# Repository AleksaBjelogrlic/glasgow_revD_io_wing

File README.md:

# glasgow_revD_io_wing

Modular test board for Glasgow RevD IO ports. Four of these will connect to a core board to form a complete revD prototype. Doing unconstrained and modular designs will speed up iteration and get us to a finalized design faster.

## Design Goals:

### 1.2V VIO support

- Use 74AXP1T45 level shifters as per [Glasgow #283](https://github.com/GlasgowEmbedded/glasgow/issues/283). 
- No GPIO expander will support this voltage so we have to do something clever for the programmable pulls.
- Pulldowns added on DIR pins as per [Glasgow #552, option 2](https://github.com/GlasgowEmbedded/glasgow/issues/552).
- Option 3 will not work at VIO = 5V as DIR is on the port A side and would be fed with a 3.3V signal, which is lower than the 3.5V threshold for VCCA = 5V.

### Increase VIO output current and support true 5V VIO

- Use a buck-boost regulator, TPS631012 eliminates the need for a DAC as well
- Max 1.5A on each port, can go up to 5.5V regardless of VUSB

### Make the most out of any USB host without browning out

- Adustable current limits on all VIO regulator inputs for 500mA, 1.5A, and 3A capable USB hosts  

### Add a user analog input

- Use the two free pins on each Glasgow port
- Single ended or diff, for voltage and current monitoring on the user's board

### Test new ESD diode array

- [Glasgow #765](https://github.com/GlasgowEmbedded/glasgow/issues/765)

### Improve schematic readablity

- Make the functions of the IO ports as clear as possible from first glance

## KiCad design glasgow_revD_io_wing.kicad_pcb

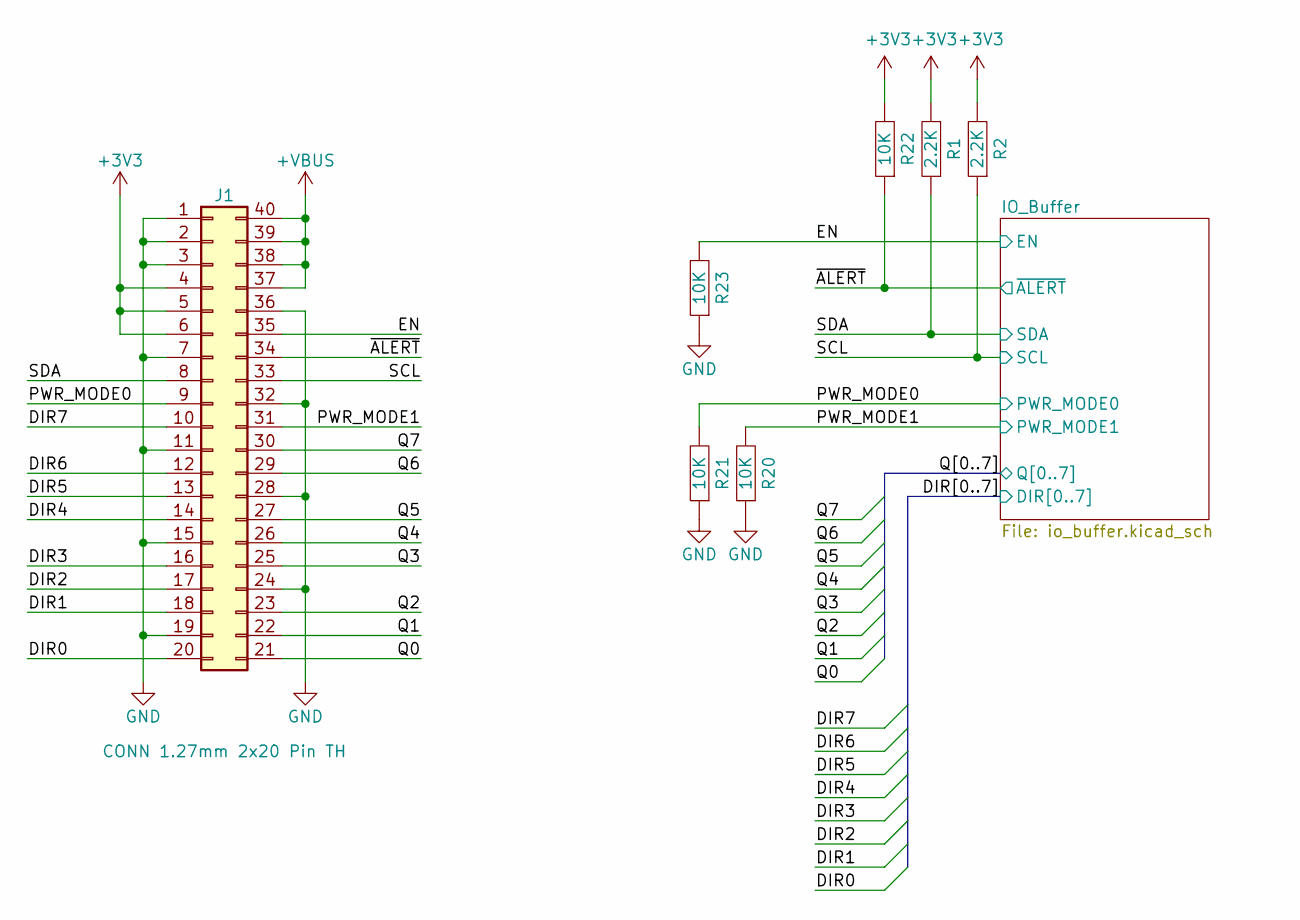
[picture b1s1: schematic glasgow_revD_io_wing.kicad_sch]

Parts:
J1: CONN 1.27mm 2x20 Pin TH; PinHeader_2x20_P1.27mm_Vertical
R1, R2: 2.2K; GEN_R_0402; TOLERANCE 1%; MANUFACTURER PART NUMBER RC0402FR-132K2L
R20, R21, R22, R23: 10K; GEN_R_0402; TOLERANCE 1%; MANUFACTURER PART NUMBER ERJ-2RKF1002X

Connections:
+3V3: J1.4, J1.5, J1.6, R1.1, R2.1, R22.2; also elsewhere on the board
+VBUS: J1.37, J1.38, J1.39, J1.40; also elsewhere on the board
/DIR0: J1.20; also elsewhere on the board
/DIR1: J1.18; also elsewhere on the board
/DIR2: J1.17; also elsewhere on the board
/DIR3: J1.16; also elsewhere on the board
/DIR4: J1.14; also elsewhere on the board
/DIR5: J1.13; also elsewhere on the board
/DIR6: J1.12; also elsewhere on the board
/DIR7: J1.10; also elsewhere on the board
/EN: J1.35, R23.2; also elsewhere on the board
/PWR_MODE0: J1.9, R21.2; also elsewhere on the board
/PWR_MODE1: J1.31, R20.2; also elsewhere on the board
/Q0: J1.21; also elsewhere on the board
/Q1: J1.22; also elsewhere on the board
/Q2: J1.23; also elsewhere on the board
/Q3: J1.25; also elsewhere on the board
/Q4: J1.26; also elsewhere on the board
/Q5: J1.27; also elsewhere on the board
/Q6: J1.29; also elsewhere on the board
/Q7: J1.30; also elsewhere on the board
/SCL: J1.33, R2.2; also elsewhere on the board
/SDA: J1.8, R1.2; also elsewhere on the board
/~ALERT: J1.34, R22.1; also elsewhere on the board
GND: J1.1, J1.2, J1.3, J1.7, J1.11, J1.15, J1.19, J1.24, J1.28, J1.32, J1.36, R20.1, R21.1, R23.1; also elsewhere on the board

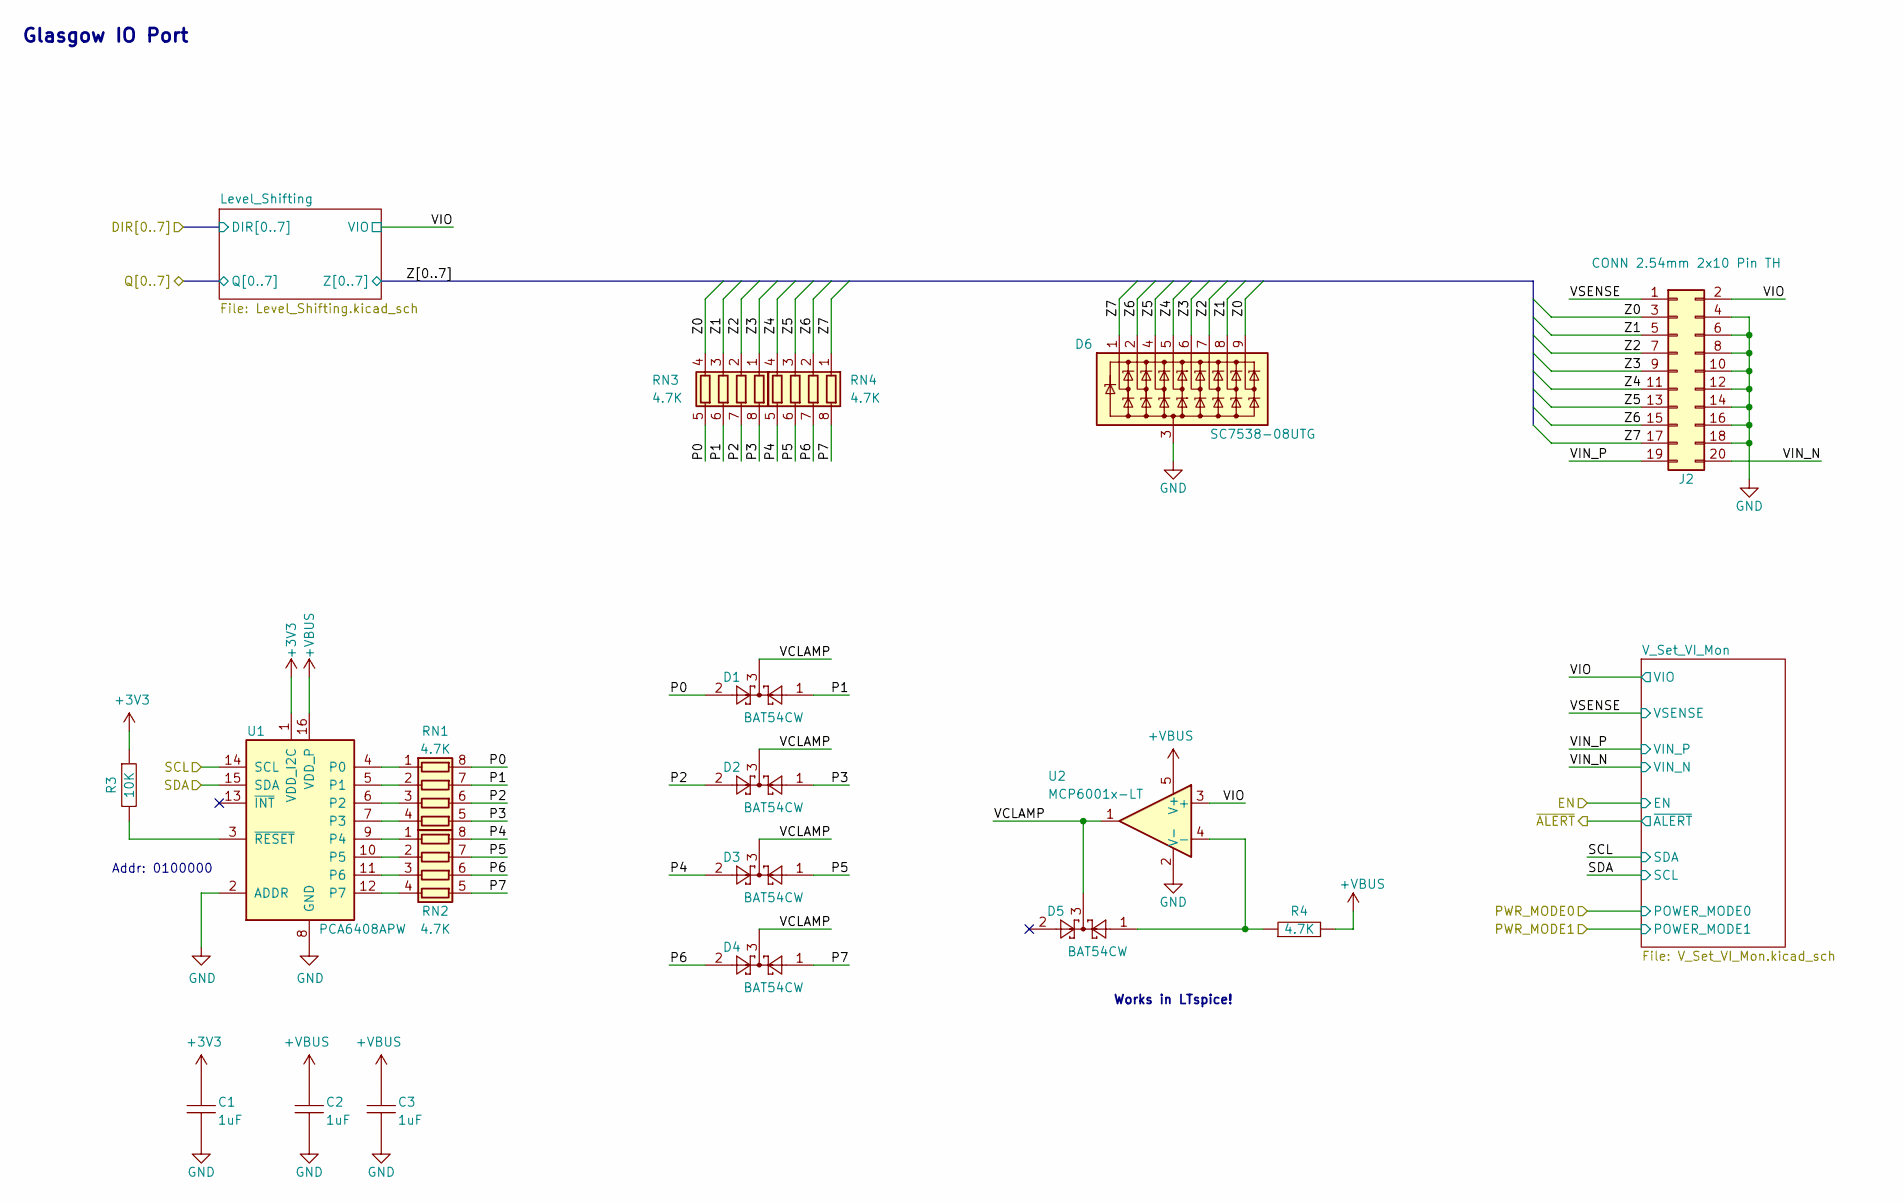
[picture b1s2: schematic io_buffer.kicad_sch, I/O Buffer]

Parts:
C1, C2, C3: 1uF; GEN_C_0402; VOLTAGE RATING 25V; MANUFACTURER PART NUMBER GRM155R61E105KA12D
D1, D2, D3, D4, D5: BAT54CW; SOT-323_SC-70; MANUFACTURER PART NUMBER BAT54CW-7-F
D6: SC7538-08UTG; Littelfuse_UDFN-9_1.0x3.8mm_P0.5mm; MANUFACTURER PART NUMBER SC7538-08UTG
J2: CONN 2.54mm 2x10 Pin TH; IDC-Header_2x10_P2.54mm_Vertical; MANUFACTURER PART NUMBER 87834-2019
R3: 10K; GEN_R_0402; TOLERANCE 1%; MANUFACTURER PART NUMBER ERJ-2RKF1002X
R4: 4.7K; GEN_R_0402; TOLERANCE 1%; MANUFACTURER PART NUMBER ERJ-2RKF4701X
RN1, RN2, RN3, RN4: 4.7K; R_Array_Convex_4x0402; MANUFACTURER PART NUMBER YC124-FR-074K7L
U1: PCA6408APW; TSSOP-16_4.4x5mm_P0.65mm; MANUFACTURER PART NUMBER PCA6408APW
U2: MCP6001x-LT; SOT-353_SC-70-5; MANUFACTURER PART NUMBER MCP6001T-I/LT

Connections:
+3V3: C1.1, R3.1, U1.1 (VDD_I2C); also elsewhere on the board
+VBUS: C2.1, C3.1, R4.1, U1.16 (VDD_P), U2.5 (V+); also elsewhere on the board
/IO_Buffer/P0: D1.2, RN1.8 (R1.2), RN3.5 (R4.2)
/IO_Buffer/P1: D1.1, RN1.7 (R2.2), RN3.6 (R3.2)
/IO_Buffer/P2: D2.2, RN1.6 (R3.2), RN3.7 (R2.2)
/IO_Buffer/P3: D2.1, RN1.5 (R4.2), RN3.8 (R1.2)
/IO_Buffer/P4: D3.2, RN2.8 (R1.2), RN4.5 (R4.2)
/IO_Buffer/P5: D3.1, RN2.7 (R2.2), RN4.6 (R3.2)
/IO_Buffer/P6: D4.2, RN2.6 (R3.2), RN4.7 (R2.2)
/IO_Buffer/P7: D4.1, RN2.5 (R4.2), RN4.8 (R1.2)
/IO_Buffer/VCLAMP: D1.3, D2.3, D3.3, D4.3, D5.3, U2.1
/IO_Buffer/VIN_N: J2.20; also elsewhere on the board
/IO_Buffer/VIN_P: J2.19; also elsewhere on the board
/IO_Buffer/VIO: J2.2, U2.3 (+); also elsewhere on the board
/IO_Buffer/VSENSE: J2.1; also elsewhere on the board
/IO_Buffer/Z0: D6.9 (K8), J2.3, RN3.4 (R4.1); also elsewhere on the board
/IO_Buffer/Z1: D6.8 (K7), J2.5, RN3.3 (R3.1); also elsewhere on the board
/IO_Buffer/Z2: D6.7 (K6), J2.7, RN3.2 (R2.1); also elsewhere on the board
/IO_Buffer/Z3: D6.6 (K5), J2.9, RN3.1 (R1.1); also elsewhere on the board
/IO_Buffer/Z4: D6.5 (K4), J2.11, RN4.4 (R4.1); also elsewhere on the board
/IO_Buffer/Z5: D6.4 (K3), J2.13, RN4.3 (R3.1); also elsewhere on the board
/IO_Buffer/Z6: D6.2 (K2), J2.15, RN4.2 (R2.1); also elsewhere on the board
/IO_Buffer/Z7: D6.1 (K1), J2.17, RN4.1 (R1.1); also elsewhere on the board
/SCL: U1.14 (SCL); also elsewhere on the board
/SDA: U1.15 (SDA); also elsewhere on the board
GND: C1.2, C2.2, C3.2, D6.3 (A), J2.4, J2.6, J2.8, J2.10, J2.12, J2.14, J2.16, J2.18, U1.2 (ADDR), U1.8 (GND), U2.2 (V-); also elsewhere on the board
unnamed: RN1.1 (R1.1), U1.4 (P0)
unnamed: RN1.2 (R2.1), U1.5 (P1)
unnamed: RN1.3 (R3.1), U1.6 (P2)
unnamed: RN1.4 (R4.1), U1.7 (P3)
unnamed: RN2.1 (R1.1), U1.9 (P4)
unnamed: RN2.2 (R2.1), U1.10 (P5)
unnamed: RN2.3 (R3.1), U1.11 (P6)
unnamed: RN2.4 (R4.1), U1.12 (P7)
unnamed: R3.2, U1.3 (~RESET)
unnamed: D5.1, R4.2, U2.4 (-)

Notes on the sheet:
Glasgow IO Port
Addr: 0100000
Works in LTspice!

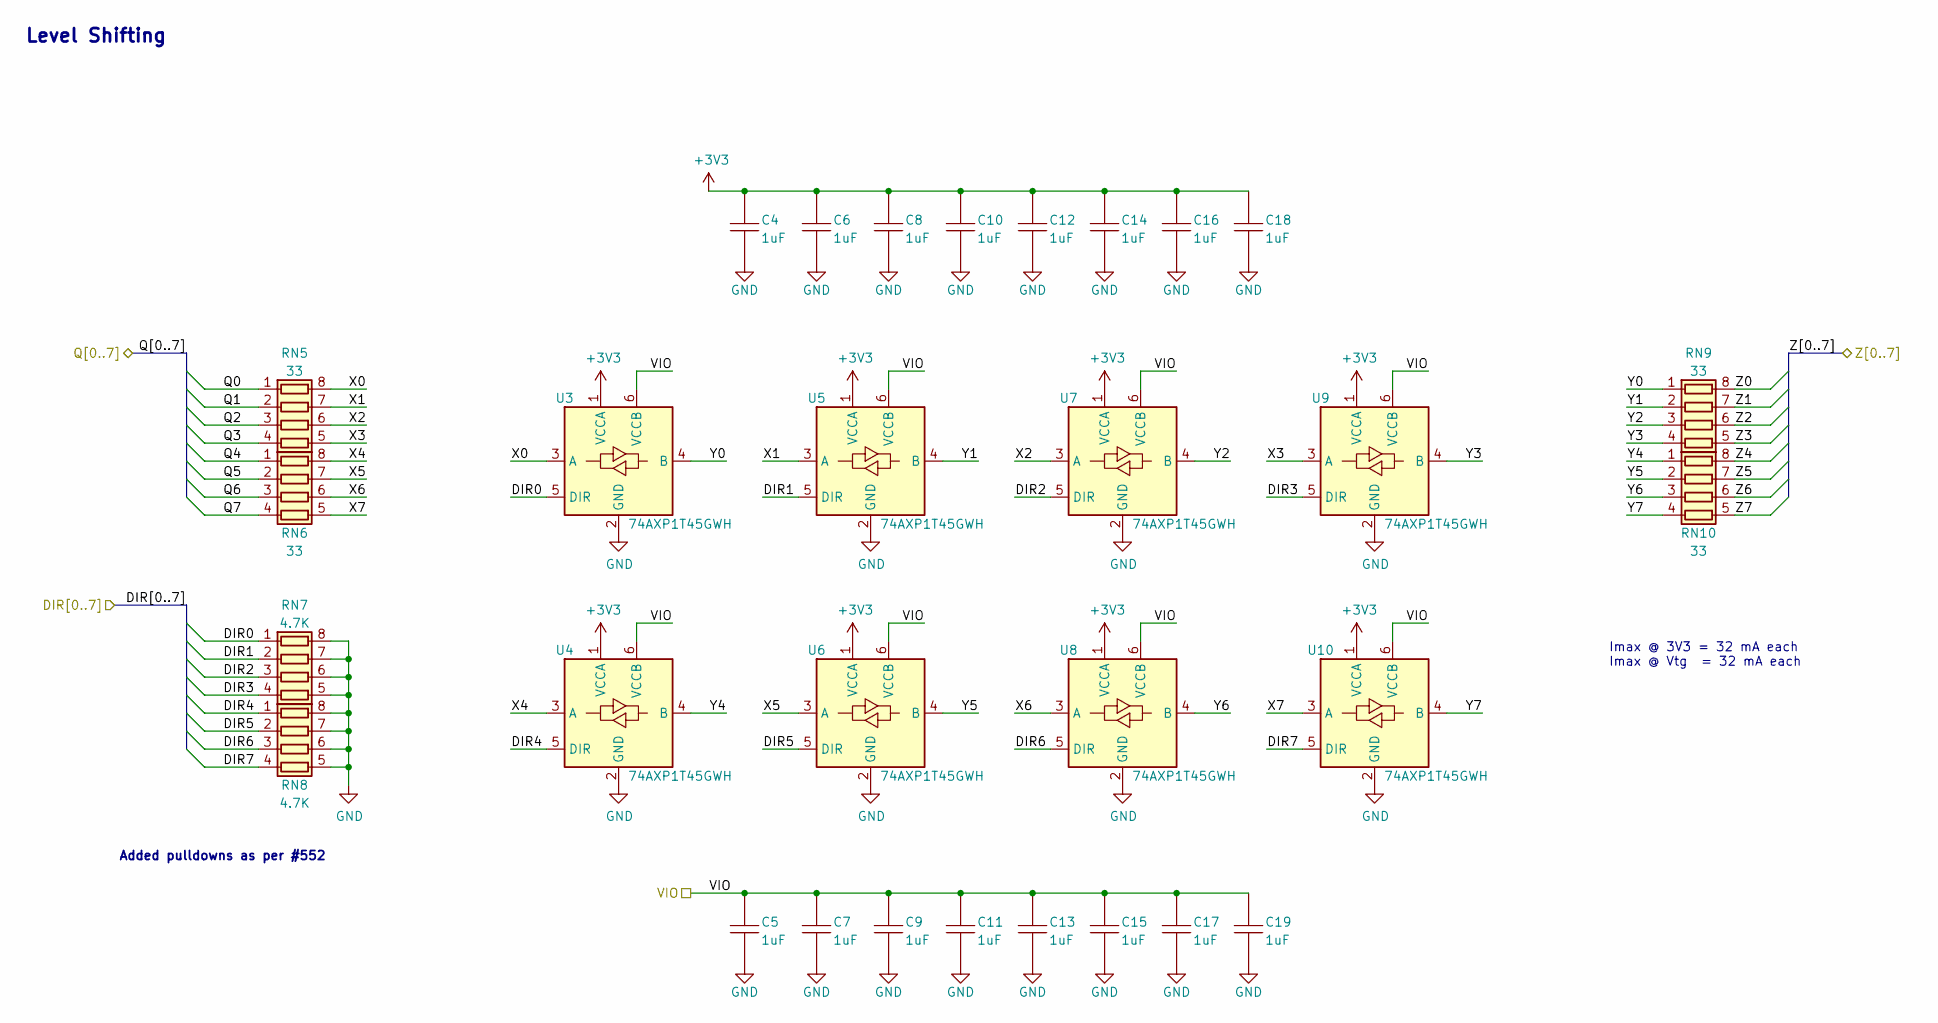
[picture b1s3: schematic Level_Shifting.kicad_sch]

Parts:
C4, C5, C6, C7, C8, C9, C10, C11, C12, C13, C14, C15, C16, C17, C18, C19: 1uF; GEN_C_0402; VOLTAGE RATING 25V; MANUFACTURER PART NUMBER GRM155R61E105KA12D
RN5, RN6, RN9, RN10: 33; R_Array_Convex_4x0402; MANUFACTURER PART NUMBER YC124-JR-1333RL
RN7, RN8: 4.7K; R_Array_Convex_4x0402; MANUFACTURER PART NUMBER YC124-FR-074K7L
U3, U4, U5, U6, U7, U8, U9, U10: 74AXP1T45GWH; SOT-363_SC-70-6; MANUFACTURER PART NUMBER 74AXP1T45GWH

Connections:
+3V3: C4.1, C6.1, C8.1, C10.1, C12.1, C14.1, C16.1, C18.1, U3.1 (VCCA), U4.1 (VCCA), U5.1 (VCCA), U6.1 (VCCA), U7.1 (VCCA), U8.1 (VCCA), U9.1 (VCCA), U10.1 (VCCA); also elsewhere on the board
/DIR0: RN7.1 (R1.1), U3.5 (DIR); also elsewhere on the board
/DIR1: RN7.2 (R2.1), U5.5 (DIR); also elsewhere on the board
/DIR2: RN7.3 (R3.1), U7.5 (DIR); also elsewhere on the board
/DIR3: RN7.4 (R4.1), U9.5 (DIR); also elsewhere on the board
/DIR4: RN8.1 (R1.1), U4.5 (DIR); also elsewhere on the board
/DIR5: RN8.2 (R2.1), U6.5 (DIR); also elsewhere on the board
/DIR6: RN8.3 (R3.1), U8.5 (DIR); also elsewhere on the board
/DIR7: RN8.4 (R4.1), U10.5 (DIR); also elsewhere on the board
/IO_Buffer/Level_Shifting/X0: RN5.8 (R1.2), U3.3 (A)
/IO_Buffer/Level_Shifting/X1: RN5.7 (R2.2), U5.3 (A)
/IO_Buffer/Level_Shifting/X2: RN5.6 (R3.2), U7.3 (A)
/IO_Buffer/Level_Shifting/X3: RN5.5 (R4.2), U9.3 (A)
/IO_Buffer/Level_Shifting/X4: RN6.8 (R1.2), U4.3 (A)
/IO_Buffer/Level_Shifting/X5: RN6.7 (R2.2), U6.3 (A)
/IO_Buffer/Level_Shifting/X6: RN6.6 (R3.2), U8.3 (A)
/IO_Buffer/Level_Shifting/X7: RN6.5 (R4.2), U10.3 (A)
/IO_Buffer/Level_Shifting/Y0: RN9.1 (R1.1), U3.4 (B)
/IO_Buffer/Level_Shifting/Y1: RN9.2 (R2.1), U5.4 (B)
/IO_Buffer/Level_Shifting/Y2: RN9.3 (R3.1), U7.4 (B)
/IO_Buffer/Level_Shifting/Y3: RN9.4 (R4.1), U9.4 (B)
/IO_Buffer/Level_Shifting/Y4: RN10.1 (R1.1), U4.4 (B)
/IO_Buffer/Level_Shifting/Y5: RN10.2 (R2.1), U6.4 (B)
/IO_Buffer/Level_Shifting/Y6: RN10.3 (R3.1), U8.4 (B)
/IO_Buffer/Level_Shifting/Y7: RN10.4 (R4.1), U10.4 (B)
/IO_Buffer/VIO: C5.1, C7.1, C9.1, C11.1, C13.1, C15.1, C17.1, C19.1, U3.6 (VCCB), U4.6 (VCCB), U5.6 (VCCB), U6.6 (VCCB), U7.6 (VCCB), U8.6 (VCCB), U9.6 (VCCB), U10.6 (VCCB); also elsewhere on the board
/IO_Buffer/Z0: RN9.8 (R1.2); also elsewhere on the board
/IO_Buffer/Z1: RN9.7 (R2.2); also elsewhere on the board
/IO_Buffer/Z2: RN9.6 (R3.2); also elsewhere on the board
/IO_Buffer/Z3: RN9.5 (R4.2); also elsewhere on the board
/IO_Buffer/Z4: RN10.8 (R1.2); also elsewhere on the board
/IO_Buffer/Z5: RN10.7 (R2.2); also elsewhere on the board
/IO_Buffer/Z6: RN10.6 (R3.2); also elsewhere on the board
/IO_Buffer/Z7: RN10.5 (R4.2); also elsewhere on the board
/Q0: RN5.1 (R1.1); also elsewhere on the board
/Q1: RN5.2 (R2.1); also elsewhere on the board
/Q2: RN5.3 (R3.1); also elsewhere on the board
/Q3: RN5.4 (R4.1); also elsewhere on the board
/Q4: RN6.1 (R1.1); also elsewhere on the board
/Q5: RN6.2 (R2.1); also elsewhere on the board
/Q6: RN6.3 (R3.1); also elsewhere on the board
/Q7: RN6.4 (R4.1); also elsewhere on the board
GND: C4.2, C5.2, C6.2, C7.2, C8.2, C9.2, C10.2, C11.2, C12.2, C13.2, C14.2, C15.2, C16.2, C17.2, C18.2, C19.2, RN7.5 (R4.2), RN7.6 (R3.2), RN7.7 (R2.2), RN7.8 (R1.2), RN8.5 (R4.2), RN8.6 (R3.2), RN8.7 (R2.2), RN8.8 (R1.2), U3.2 (GND), U4.2 (GND), U5.2 (GND), U6.2 (GND), U7.2 (GND), U8.2 (GND), U9.2 (GND), U10.2 (GND); also elsewhere on the board

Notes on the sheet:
Imax @ 3V3 = 32 mA each Imax @ Vtg = 32 mA each
Added pulldowns as per #552
Level Shifting

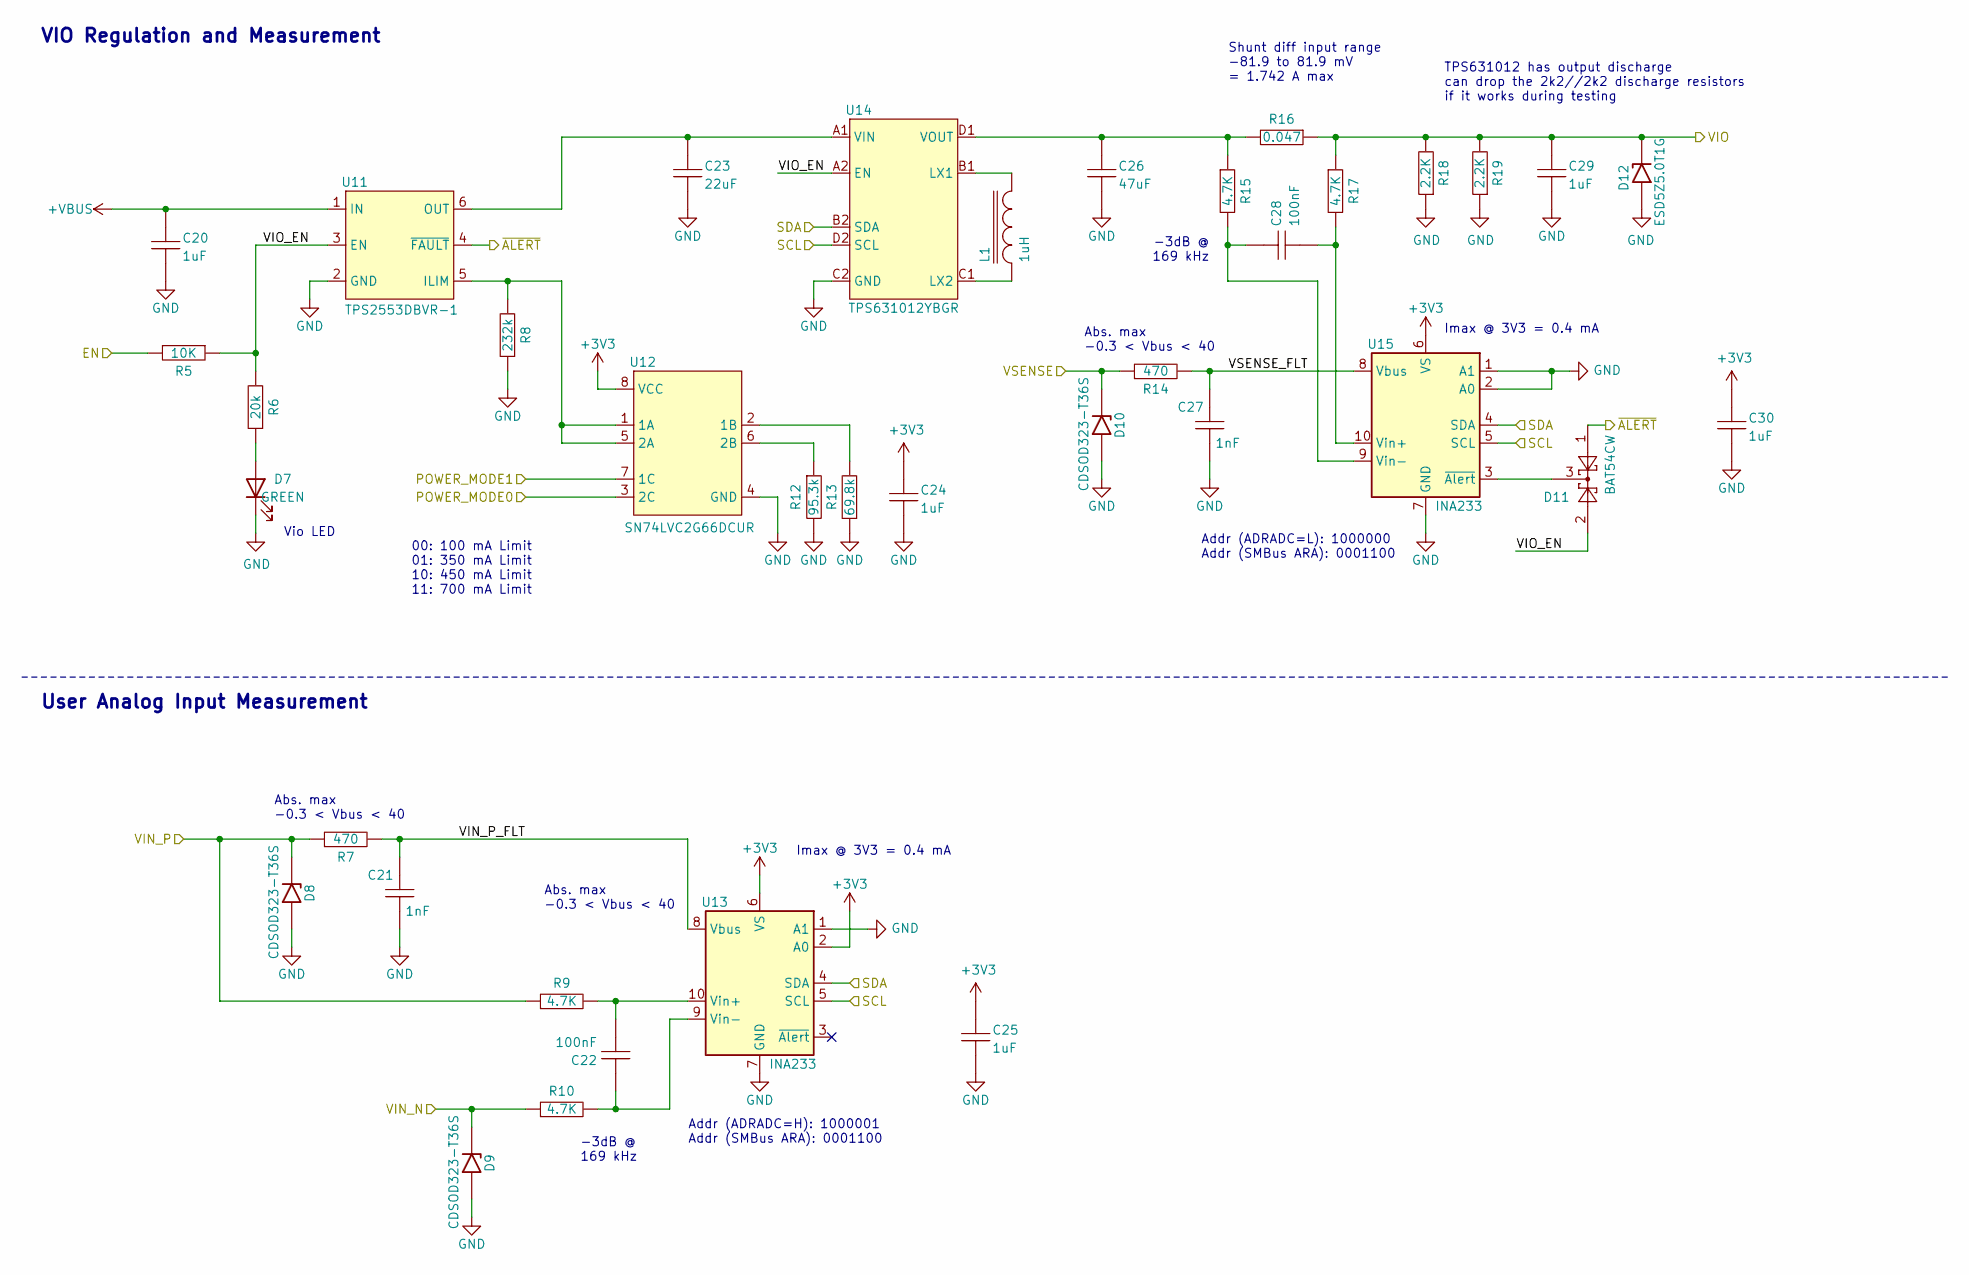
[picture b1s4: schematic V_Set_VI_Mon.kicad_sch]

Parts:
C20, C24, C25, C29, C30: 1uF; GEN_C_0402; VOLTAGE RATING 25V; MANUFACTURER PART NUMBER GRM155R61E105KA12D
C21, C27: 1nF; GEN_C_0402; VOLTAGE RATING 50V; MANUFACTURER PART NUMBER GRM1555C1H102FA01D
C22, C28: 100nF; GEN_C_0402; VOLTAGE RATING 16V; MANUFACTURER PART NUMBER GCM155R71C104KA55D
C23: 22uF; GEN_C_0805; VOLTAGE RATING 25V; MANUFACTURER PART NUMBER GRM21BR61E226ME44L
C26: 47uF; GEN_C_0805; VOLTAGE RATING 6.3V; MANUFACTURER PART NUMBER CL21A476MQYNNNE
D7: GREEN; LED_0603_1608Metric; MANUFACTURER PART NUMBER NCD0603G1
D8, D9, D10: CDSOD323-T36S; D_SOD-323; MANUFACTURER PART NUMBER CDSOD323-T36S
D11: BAT54CW; SOT-323_SC-70; MANUFACTURER PART NUMBER BAT54CW-7-F
D12: ESD5Z5.0T1G; D_SOD-323; MANUFACTURER PART NUMBER ESD5Z5.0T1G
L1: 1uH; GEN_L_1210; MANUFACTURER PART NUMBER SRP3212-1R0M
R5: 10K; GEN_R_0402; TOLERANCE 1%; MANUFACTURER PART NUMBER ERJ-2RKF1002X
R6: 20k; GEN_R_0402; TOLERANCE 1%; MANUFACTURER PART NUMBER RC0402FR-0720KL
R7, R14: 470; GEN_R_0402; TOLERANCE 1%; MANUFACTURER PART NUMBER RC0402FR-07470RL
R8: 232k; GEN_R_0402; TOLERANCE 1%; MANUFACTURER PART NUMBER RC0402FR-13232KL
R9, R10, R15, R17: 4.7K; GEN_R_0402; TOLERANCE 1%; MANUFACTURER PART NUMBER ERJ-2RKF4701X
R12: 95.3k; GEN_R_0402; TOLERANCE 1%; MANUFACTURER PART NUMBER RC0402FR-0795K3L
R13: 69.8k; GEN_R_0402; TOLERANCE 1%; MANUFACTURER PART NUMBER RC0402FR-0769K8L
R16: 0.047; GEN_R_0603; TOLERANCE 1%; MANUFACTURER PART NUMBER RL0816T-R047-F
R18, R19: 2.2K; GEN_R_0402; TOLERANCE 1%; MANUFACTURER PART NUMBER RC0402FR-132K2L
U11: TPS2553DBVR-1; SOT-23-6; MANUFACTURER PART NUMBER TPS2553DBVR-1
U12: SN74LVC2G66DCUR; Texas_VSSOP-8_2x3.1mm_P0.9; MANUFACTURER PART NUMBER SN74LVC2G66DCUR
U13, U15: INA233; VSSOP-10_3x3mm_P0.5mm; MANUFACTURER PART NUMBER INA233AIDGSR
U14: TPS631012YBGR; Texas_DSBGA-8_0.9x1.9mm_Layout2x4_P0.5mm; MANUFACTURER PART NUMBER TPS631012YBGR

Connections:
+3V3: C24.1, C25.1, C30.1, U12.8 (VCC), U13.2 (A0), U13.6 (VS), U15.6 (VS); also elsewhere on the board
+VBUS: C20.1, U11.1 (IN); also elsewhere on the board
/EN: R5.2; also elsewhere on the board
/IO_Buffer/VIN_N: D9.1 (K), R10.2; also elsewhere on the board
/IO_Buffer/VIN_P: D8.1 (K), R7.2, R9.2; also elsewhere on the board
/IO_Buffer/VIO: C29.1, D12.1 (K), R16.2, R17.2, R18.1, R19.1; also elsewhere on the board
/IO_Buffer/VSENSE: D10.1 (K), R14.2; also elsewhere on the board
/IO_Buffer/V_Set_VI_Mon/VIN_P_FLT: C21.1, R7.1, U13.8 (Vbus)
/IO_Buffer/V_Set_VI_Mon/VIO_EN: D11.2, R5.1, R6.1, U11.3 (EN), U14.A2 (EN)
/IO_Buffer/V_Set_VI_Mon/VSENSE_FLT: C27.1, R14.1, U15.8 (Vbus)
/PWR_MODE0: U12.3 (2C); also elsewhere on the board
/PWR_MODE1: U12.7 (1C); also elsewhere on the board
/SCL: U13.4 (SDA), U14.B2 (SDA), U15.4 (SDA); also elsewhere on the board
/SDA: U13.5 (SCL), U14.D2 (SCL), U15.5 (SCL); also elsewhere on the board
/~ALERT: D11.1, U11.4 (~FAULT); also elsewhere on the board
GND: C20.2, C21.2, C23.1, C24.2, C25.2, C26.1, C27.2, C29.2, C30.2, D7.1 (K), D8.2 (A), D9.2 (A), D10.2 (A), D12.2 (A), R8.2, R12.1, R13.2, R18.2, R19.2, U11.2 (GND), U12.4 (GND), U13.1 (A1), U13.7 (GND), U14.C2 (GND), U15.1 (A1), U15.2 (A0), U15.7 (GND); also elsewhere on the board
unnamed: D7.2 (A), R6.2
unnamed: R8.1, U11.5 (ILIM), U12.1 (1A), U12.5 (2A)
unnamed: C23.2, U11.6 (OUT), U14.A1 (VIN)
unnamed: R13.1, U12.2 (1B)
unnamed: R12.2, U12.6 (2B)
unnamed: C22.1, R9.1, U13.10 (Vin+)
unnamed: C22.2, R10.1, U13.9 (Vin-)
unnamed: L1.2, U14.B1 (LX1)
unnamed: L1.1, U14.C1 (LX2)
unnamed: C26.2, R15.2, R16.1, U14.D1 (VOUT)
unnamed: C28.1, R17.1, U15.10 (Vin+)
unnamed: C28.2, R15.1, U15.9 (Vin-)
unnamed: D11.3, U15.3 (~Alert)

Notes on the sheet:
Shunt diff input range -81.9 to 81.9 mV = 1.742 A max
Addr (ADRADC=H): 1000001 Addr (SMBus ARA): 0001100
Addr (ADRADC=L): 1000000 Addr (SMBus ARA): 0001100
TPS631012 has output discharge can drop the 2k2//2k2 discharge resistors if it works during testing
Abs. max -0.3 < Vbus < 40
00: 100 mA Limit 01: 350 mA Limit 10: 450 mA Limit 11: 700 mA Limit
Imax @ 3V3 = 0.4 mA
VIO Regulation and Measurement
Vio LED
-3dB @ 169 kHz
User Analog Input Measurement

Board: 2 copper layers, 92 parts (0 on the bottom side), 88 nets, no tracks yet.
